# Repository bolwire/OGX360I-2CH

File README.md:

This project builds on the original OGX360 by Ryzee119: https://github.com/Ryzee119/ogx360/

The information provided in this repo is for informational purposes only at this time.

*****IMPORTANT******
The most recent prototype USB PCB required changes to be made, I have updated the schematic and PCB layout, and tested by modifying
the PCB I have on hand, however caution should be used until the new prototype is verified. Once I have verified the changes I will remove this
notice.

The ATMEGA32U4 chips will need to be programmed with the arduino bootloader before they are put on the PCB. One option may be to remove the chips
from an arduino and transplant them. I accomplish this currently by using a jig that I will release the files for at a later time.

More will be added to this repo as I find time over the next week.

Please respect the license files found within this project. What we do, and the joy we gain from that would not be possible without those who shared the
information with us to start with. Please respect and honor that by doing the same with any works derived from this or other projects linked to in this repo.

Also my spelling sucks, so I apologize for any type-ohs that exist.

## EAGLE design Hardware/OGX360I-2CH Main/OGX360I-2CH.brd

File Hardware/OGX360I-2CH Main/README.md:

# OGX360I-2CH Main PCB.
This board was designed using [Autodesk Eagle](https://www.autodesk.com/products/eagle/overview). You can edit the `.brd` and `.sch` with this program.

## Printed Circuit Board
When fabricating your own, you can download the premade gerbers or generate your own. Suggested PCB properties are:  <br>
*2 layers, 35x71mm, 1.6mm thick, HASL, 1oz copper, no castellated holes, any colour you want!*<br>

## Bill of Materials
All the passive components listed (Resistors, capacitors etc) are listed for reference only. Any equivalents you find would be suitable. Use your best judgement. 
You should check this list against the schematic to ensure nothing is missed.  
**Digikey Quick Cart: http://www.digikey.com/short/zwrw47**  

| Qty | Value/Model | Description | Marking | URL (Passive components provided as sample only) |
| --- | --- | --- | --- | --- |
| 2 | B12B-PHDSS(LF)(SN) | CONN HEADER VERT 12POS 2MM | J4,J5 | https://www.digikey.com/product-detail/en/jst-sales-america-inc/B12B-PHDSS-LF-SN/455-1763-ND/926669 |
| 1 | ‎B6B-PH-K-S(LF)(SN) | CONN HEADER VERT 6POS 2MM | J6 | https://www.digikey.com/product-detail/en/jst-sales-america-inc/B6B-PH-K-S-LF-SN/455-1708-ND/926615 |
| 1 | MIC5219-3.3YM5-TR | IC REG LINEAR 3.3V 500MA SOT23-5‎ | U3 | https://www.digikey.com/product-detail/en/microchip-technology/MIC5219-3.3YM5-TR/576-1281-1-ND/771902 |
| 9 | 08056D104KAT2A | CAP CER 0.1UF 6.3V X5R 0805 | C1,4-5,7-8,10-11,15-16 | https://www.digikey.com/product-detail/en/avx-corporation/08056D104KAT2A/478-08056D104KAT2ACT-ND/11569296 |
| 2 | CC0805JRNPO9BN180 | CAP CER 18PF 50V C0G/NPO 0805 | C2-3 | https://www.digikey.com/product-detail/en/yageo/CC0805JRNPO9BN180/311-1102-1-ND/303012 |
| 1 | EDK106M035A9BAA | CAP ALUM 10UF 20% 35V SMD | C6 | https://www.digikey.com/product-detail/en/kemet/EDK106M035A9BAA/399-14794-1-ND/7319832 |
| 2 | C0805C105Z4VACTU | CAP CER 1UF 16V Y5V 0805 | C9, C14 | https://www.digikey.com/product-detail/en/kemet/C0805C105Z4VACTU/399-8011-1-ND/3471734 |
| 4 | C0805C220J5GACTU | CAP CER 22PF 50V C0G/NP0 0805 | C12-13,17-18 | https://www.digikey.com/product-detail/en/kemet/C0805C220J5GACTU/399-1113-1-ND/411388 |
| 2 | 10118192-0001LF | CONN RCPT USB2.0 MICRO B SMD R/A | J2-3 | https://www.digikey.com/product-detail/en/amphenol-icc-fci/10118192-0001LF/609-4613-1-ND/2785378 |
| 2 | RC0805FR-0733RL | RES SMD 33 OHM 1% 1/8W 0805 | R1-2 | https://www.digikey.com/product-detail/en/yageo/RC0805FR-0733RL/311-33.0CRCT-ND/730809 |
| 2 | RC0805FR-072KL | RES SMD 2K OHM 1% 1/8W 0805 | R3-4 | https://www.digikey.com/product-detail/en/yageo/RC0805FR-072KL/311-2.00KCRCT-ND/730611 |
| 1 | RC0805JR-071KL | RES SMD 1K OHM 5% 1/8W 0805 | R5 | https://www.digikey.com/product-detail/en/yageo/RC0805JR-071KL/311-1.0KARCT-ND/731165 |
| 4 | RC0805JR-0722RL | RES SMD 22 OHM 5% 1/8W 0805 | R6-7,9-10 | https://www.digikey.com/product-detail/en/yageo/RC0805JR-0722RL/311-22ARCT-ND/731232 |
| 2 | RC0805FR-0710KL | RES SMD 10K OHM 1% 1/8W 0805 | R8,R11 | https://www.digikey.com/product-detail/en/yageo/RC0805FR-0710KL/311-10.0KCRCT-ND/730482 |
| 1 | TL3305AF160QG | SWITCH TACTILE SPST-NO 50MA 12V | RESET | https://www.digikey.com/product-detail/en/e-switch/TL3305AF160QG/EG5350CT-ND/5816195 |
| 1 | MAX3421EEHJ+T | IC USB PERIPH/HOST CNTRL 32TQFP | U1 | https://www.digikey.com/product-detail/en/maxim-integrated/MAX3421EEHJ-T/MAX3421EEHJ-TCT-ND/4895460 |
| 1 | CD74HC4050M96 | IC BUFFER NON-INVERT 6V 16SOIC | U2 | https://www.digikey.com/product-detail/en/texas-instruments/CD74HC4050M96/296-14529-1-ND/555596 |
| 2 | ATMEGA32U4-AUR | IC MCU 8BIT 32KB FLASH 44TQFP | U4-5 | https://www.digikey.com/product-detail/en/microchip-technology/ATMEGA32U4-AUR/ATMEGA32U4-AURCT-ND/3440960 |
| 2 | TSX-3225 16.0000MF09Z-AC0 | CRYSTAL 16.0000MHZ 9PF SMD | X2-3 | https://www.digikey.com/product-detail/en/epson/TSX-3225-16.0000MF09Z-AC0/SER4069CT-ND/5413938 |
| 1 | FA-238V 12.0000MB-W3 | CRYSTAL 12.0000MHZ 12PF SMD | X1 | https://www.digikey.com/product-detail/en/epson/FA-238V-12.0000MB-W3/SER3683CT-ND/2403456 |
| 2 | PHDR-12VS | CONN HOUSING PHD 12POS 2MM DUAL | --- | https://www.digikey.com/product-detail/en/jst-sales-america-inc/PHDR-12VS/455-1204-ND/608645 |
| 10 | APAPA22K152 | JUMPER SPHD-001T-P0.5 X2 6" | --- | https://www.digikey.com/product-detail/en/jst-sales-america-inc/APAPA22K152/455-3085-ND/6009461 |
| 1 | 0ZCJ0050FF2G | PTC RESET FUSE 8V 500MA 1206 | F1 | https://www.digikey.com/product-detail/en/bel-fuse-inc/0ZCJ0050FF2G/507-1802-1-ND/4156236 |
| 2 | TMUX1237DCKR | PRECISION ANALOG MULTIPLEXER | U6-7 | https://www.digikey.com/product-detail/en/texas-instruments/TMUX1237DCKR/296-TMUX1237DCKRCT-ND/12165699 |
| 1 | SM06B-SRSS-TB(LF)(SN) | CONN HEADER SMD R/A 6POS 1MM | J7 | https://www.digikey.com/product-detail/en/jst-sales-america-inc/SM06B-SRSS-TB-LF-SN/455-1806-1-ND/926877 |

## Assembled Photo

By KingLuxor

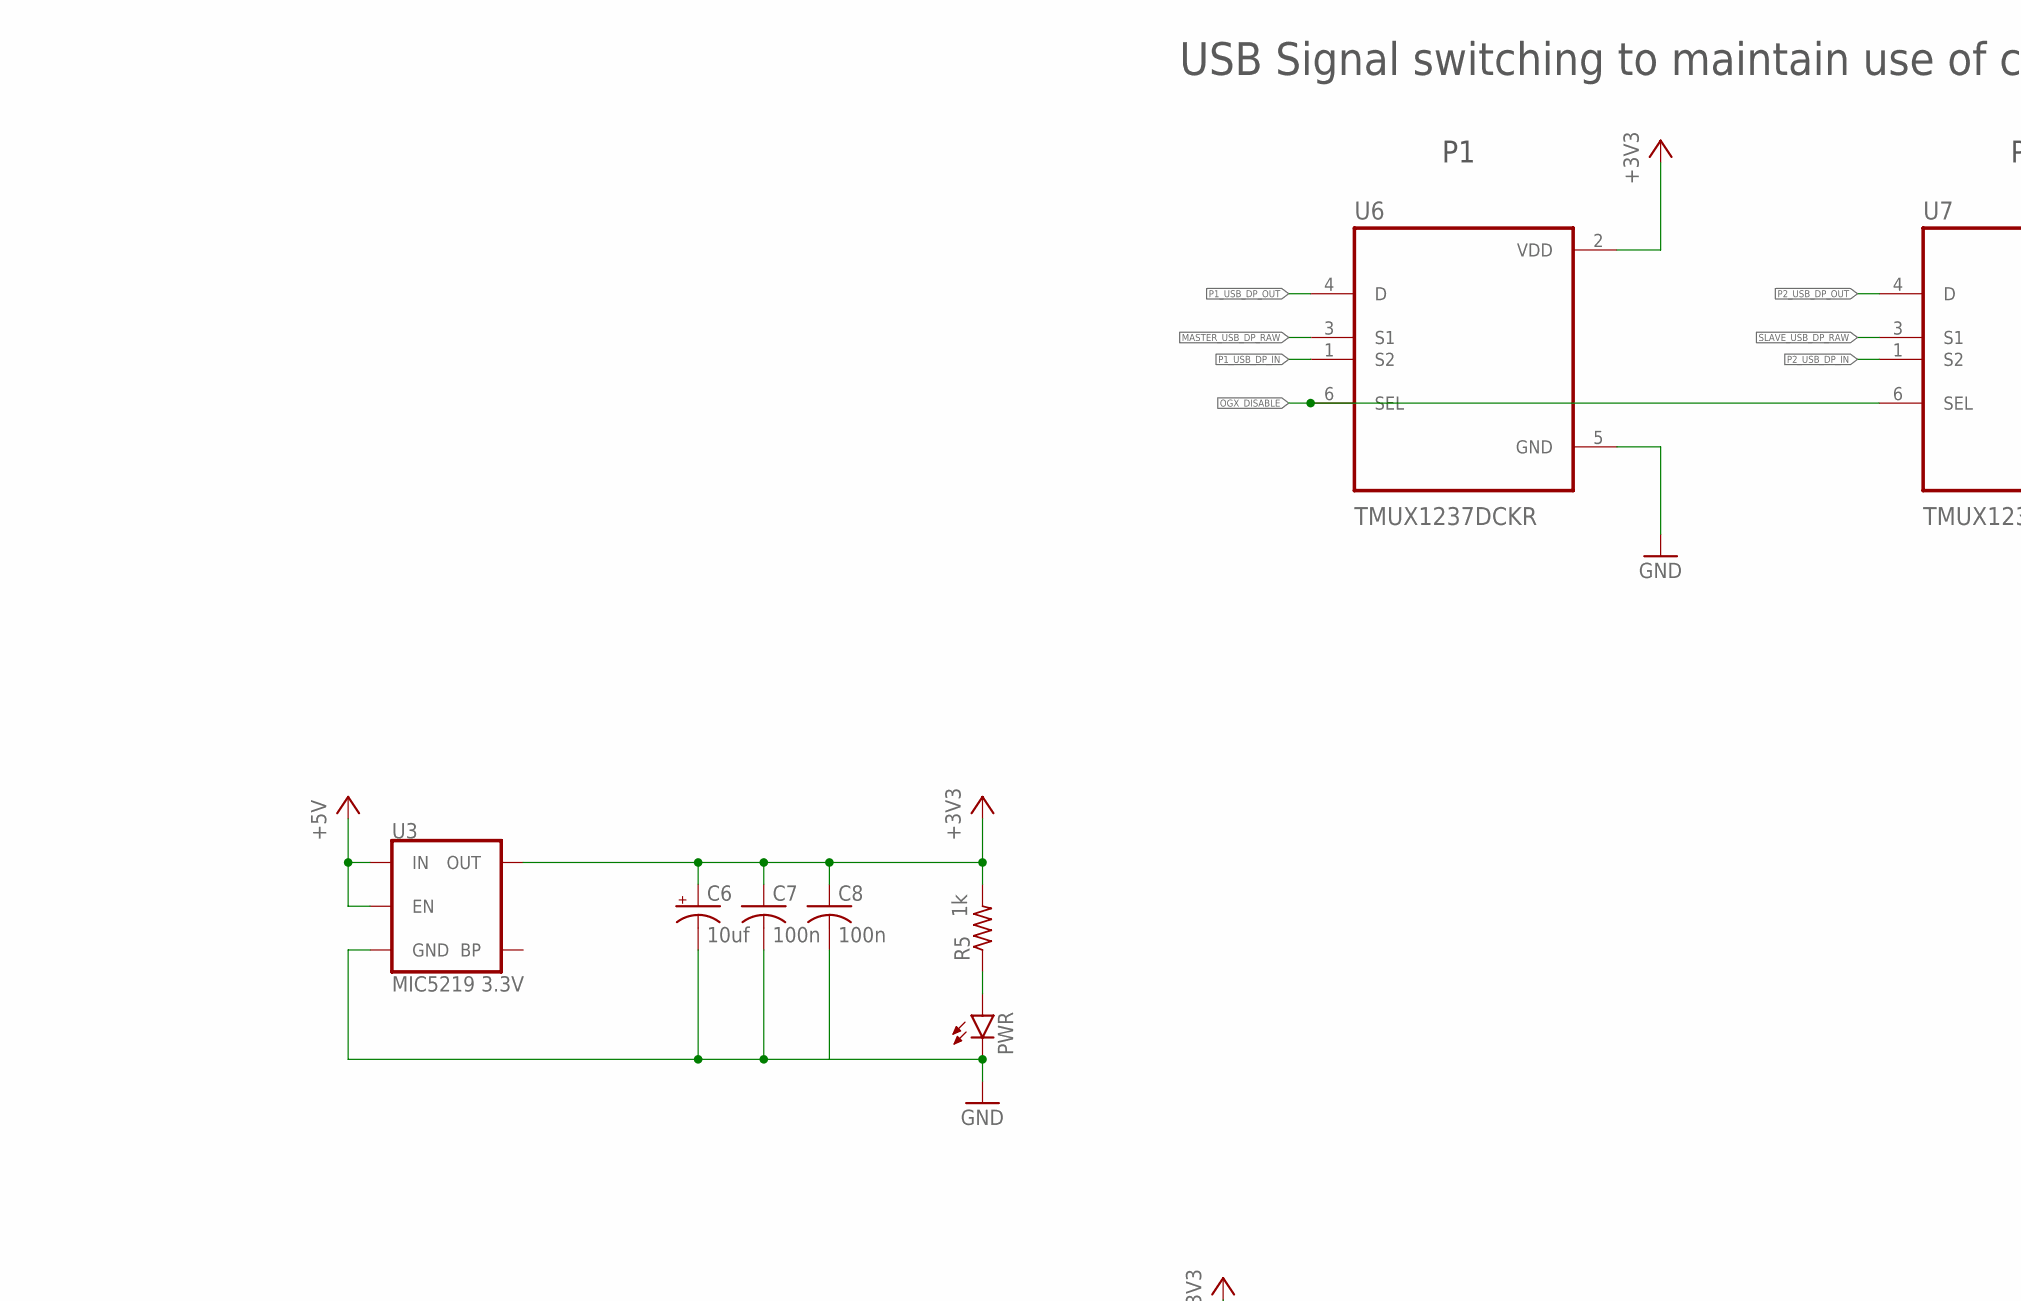
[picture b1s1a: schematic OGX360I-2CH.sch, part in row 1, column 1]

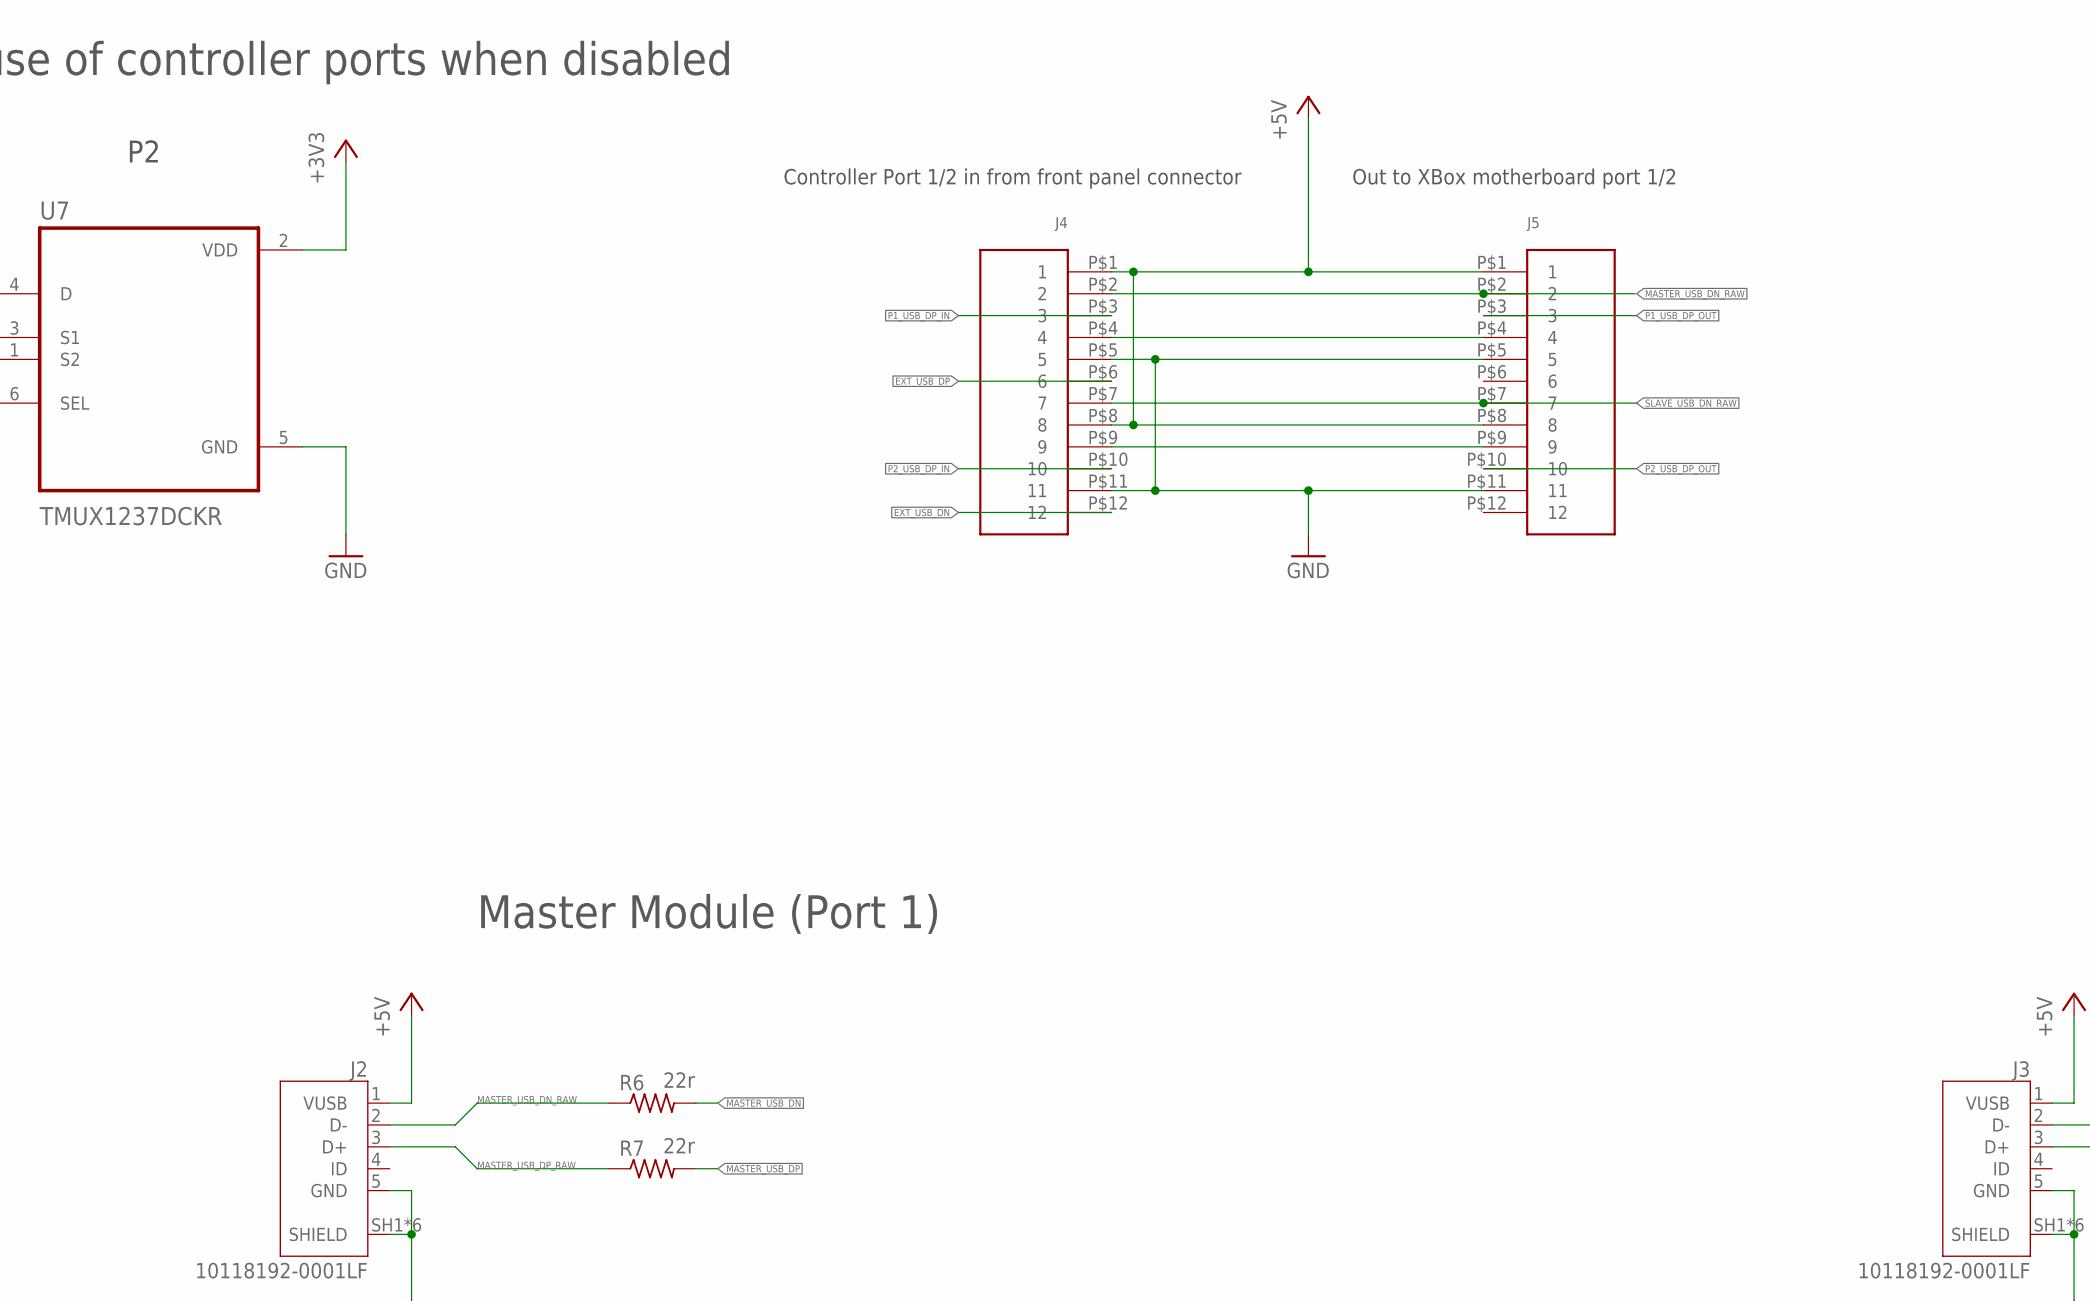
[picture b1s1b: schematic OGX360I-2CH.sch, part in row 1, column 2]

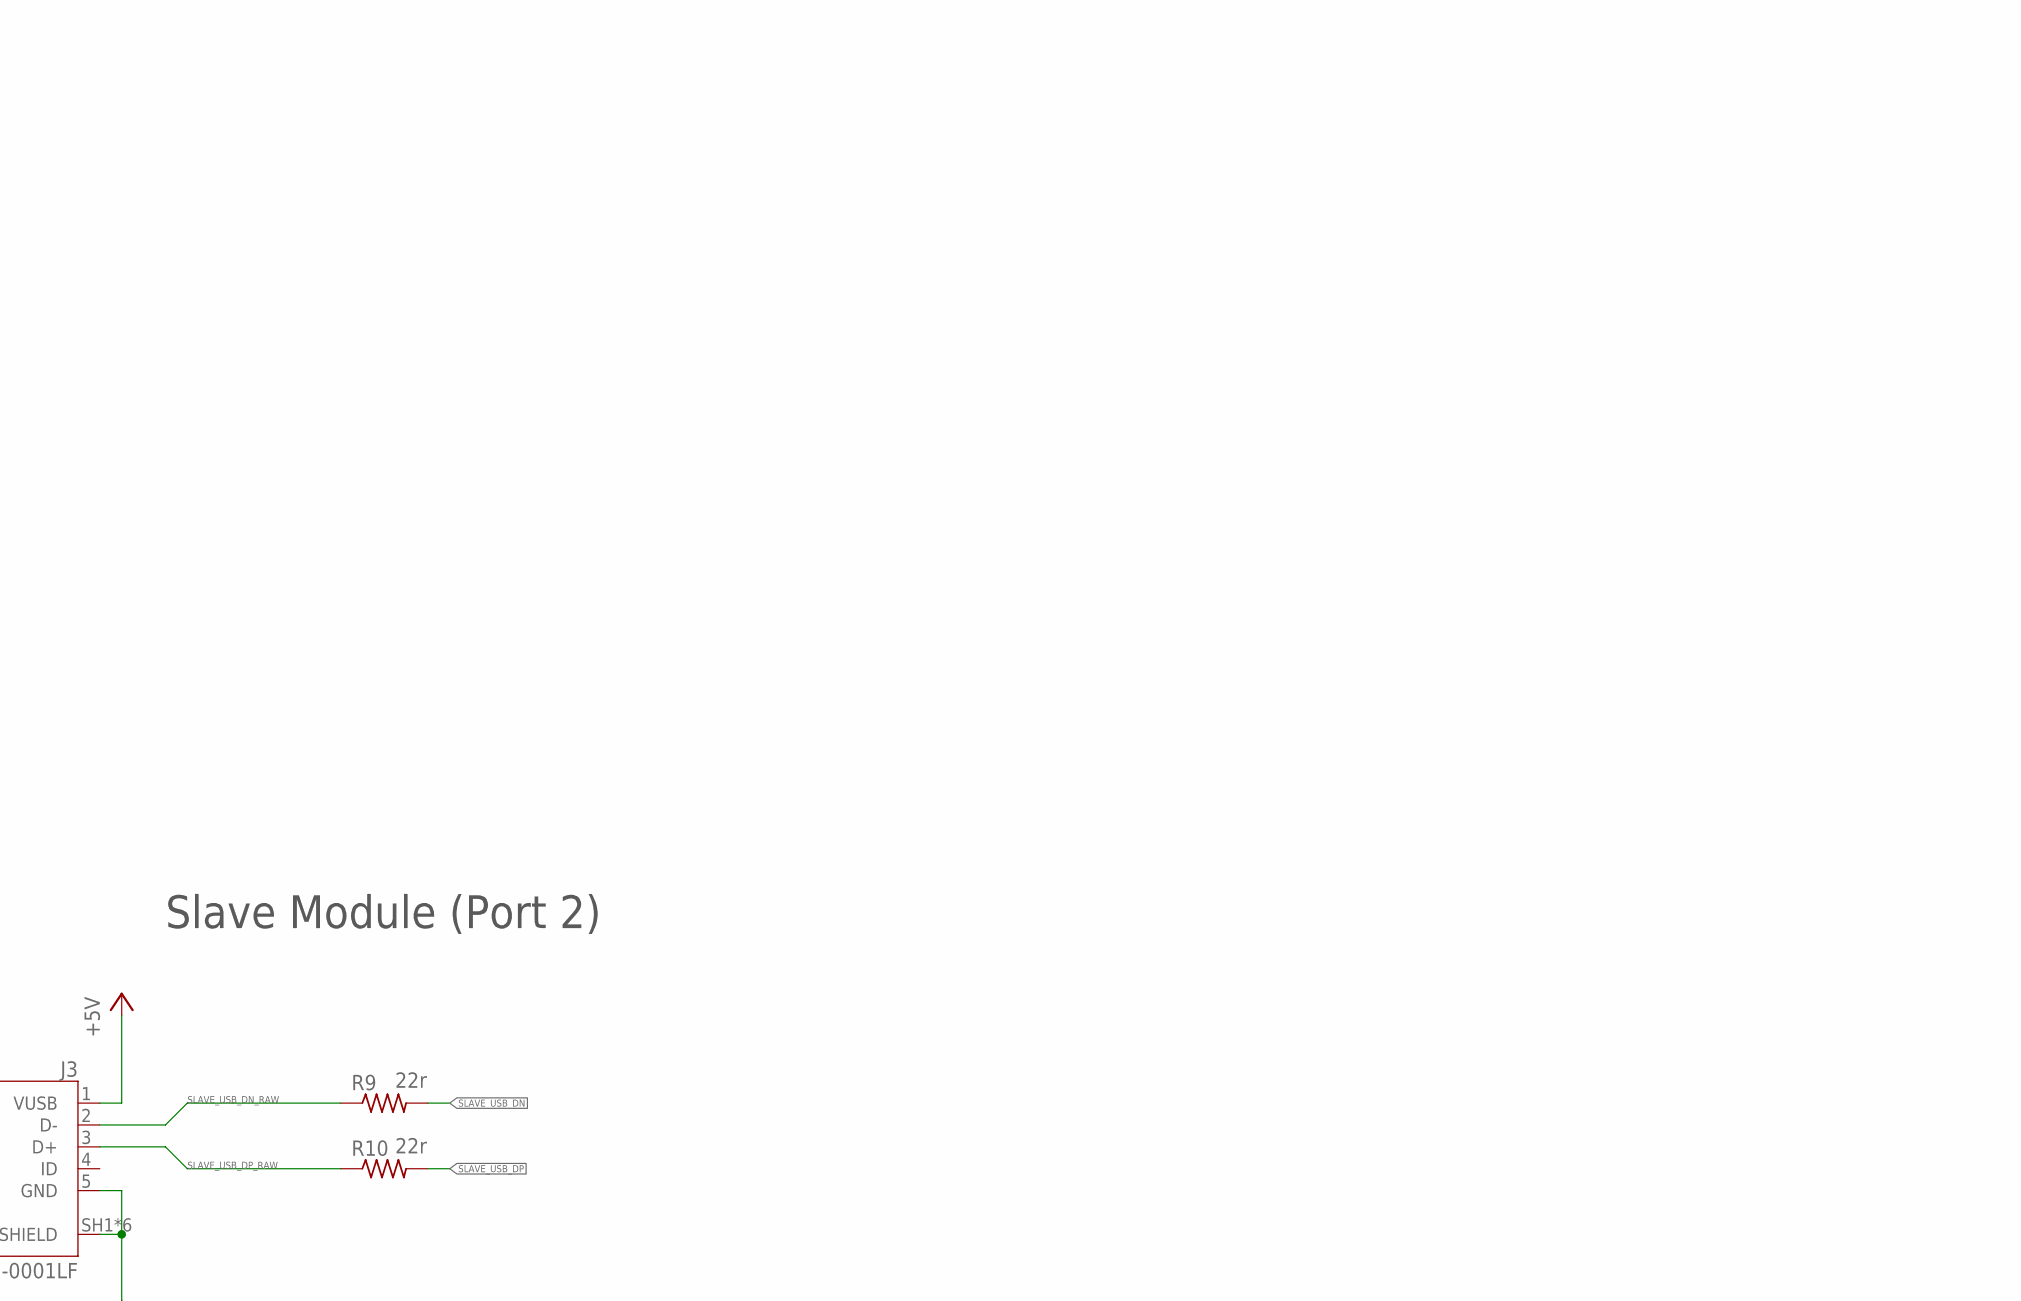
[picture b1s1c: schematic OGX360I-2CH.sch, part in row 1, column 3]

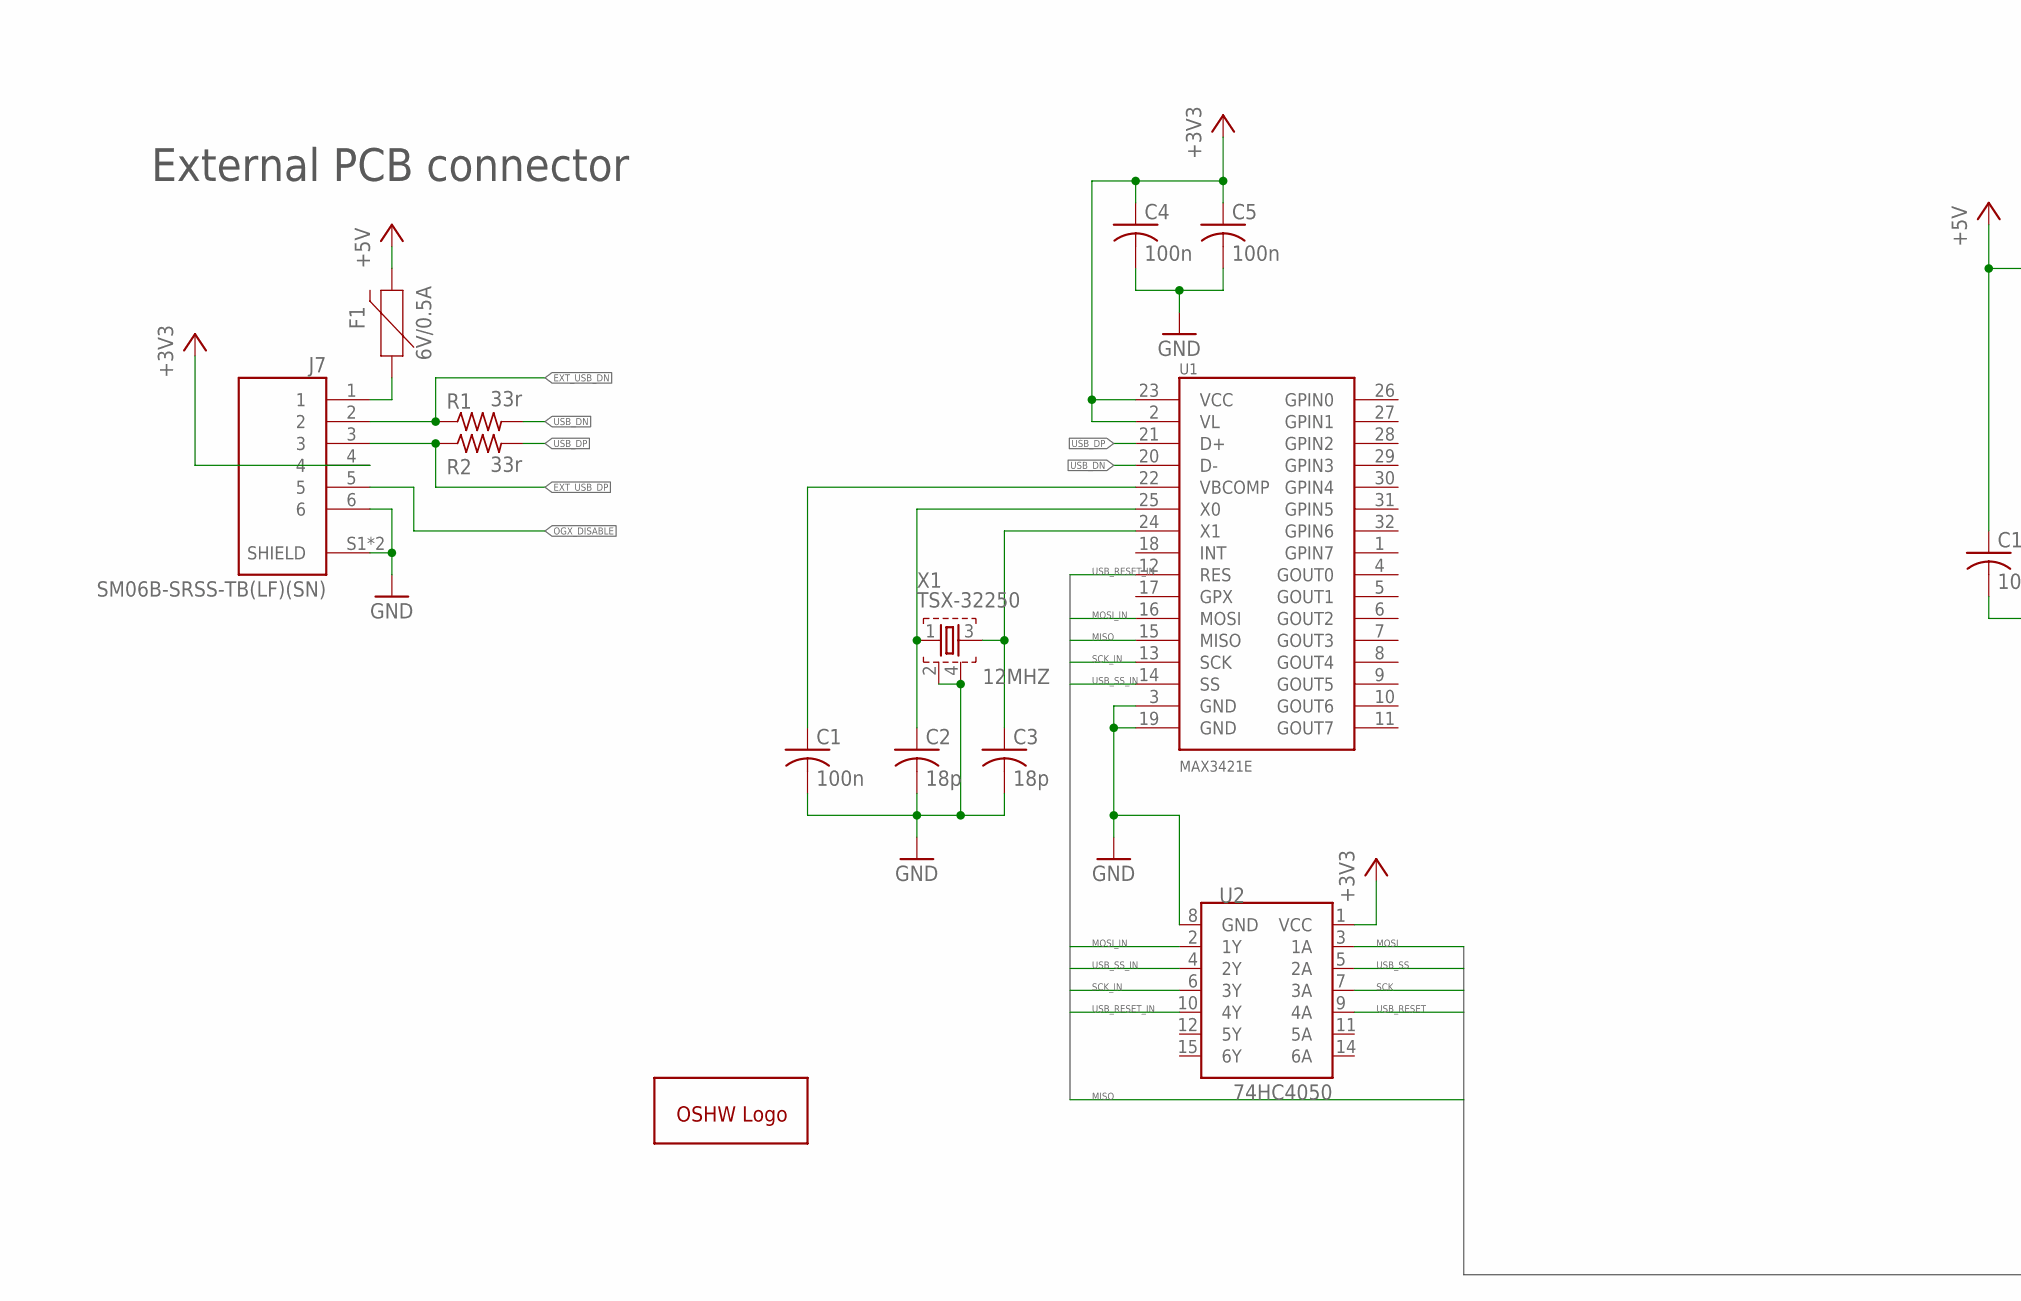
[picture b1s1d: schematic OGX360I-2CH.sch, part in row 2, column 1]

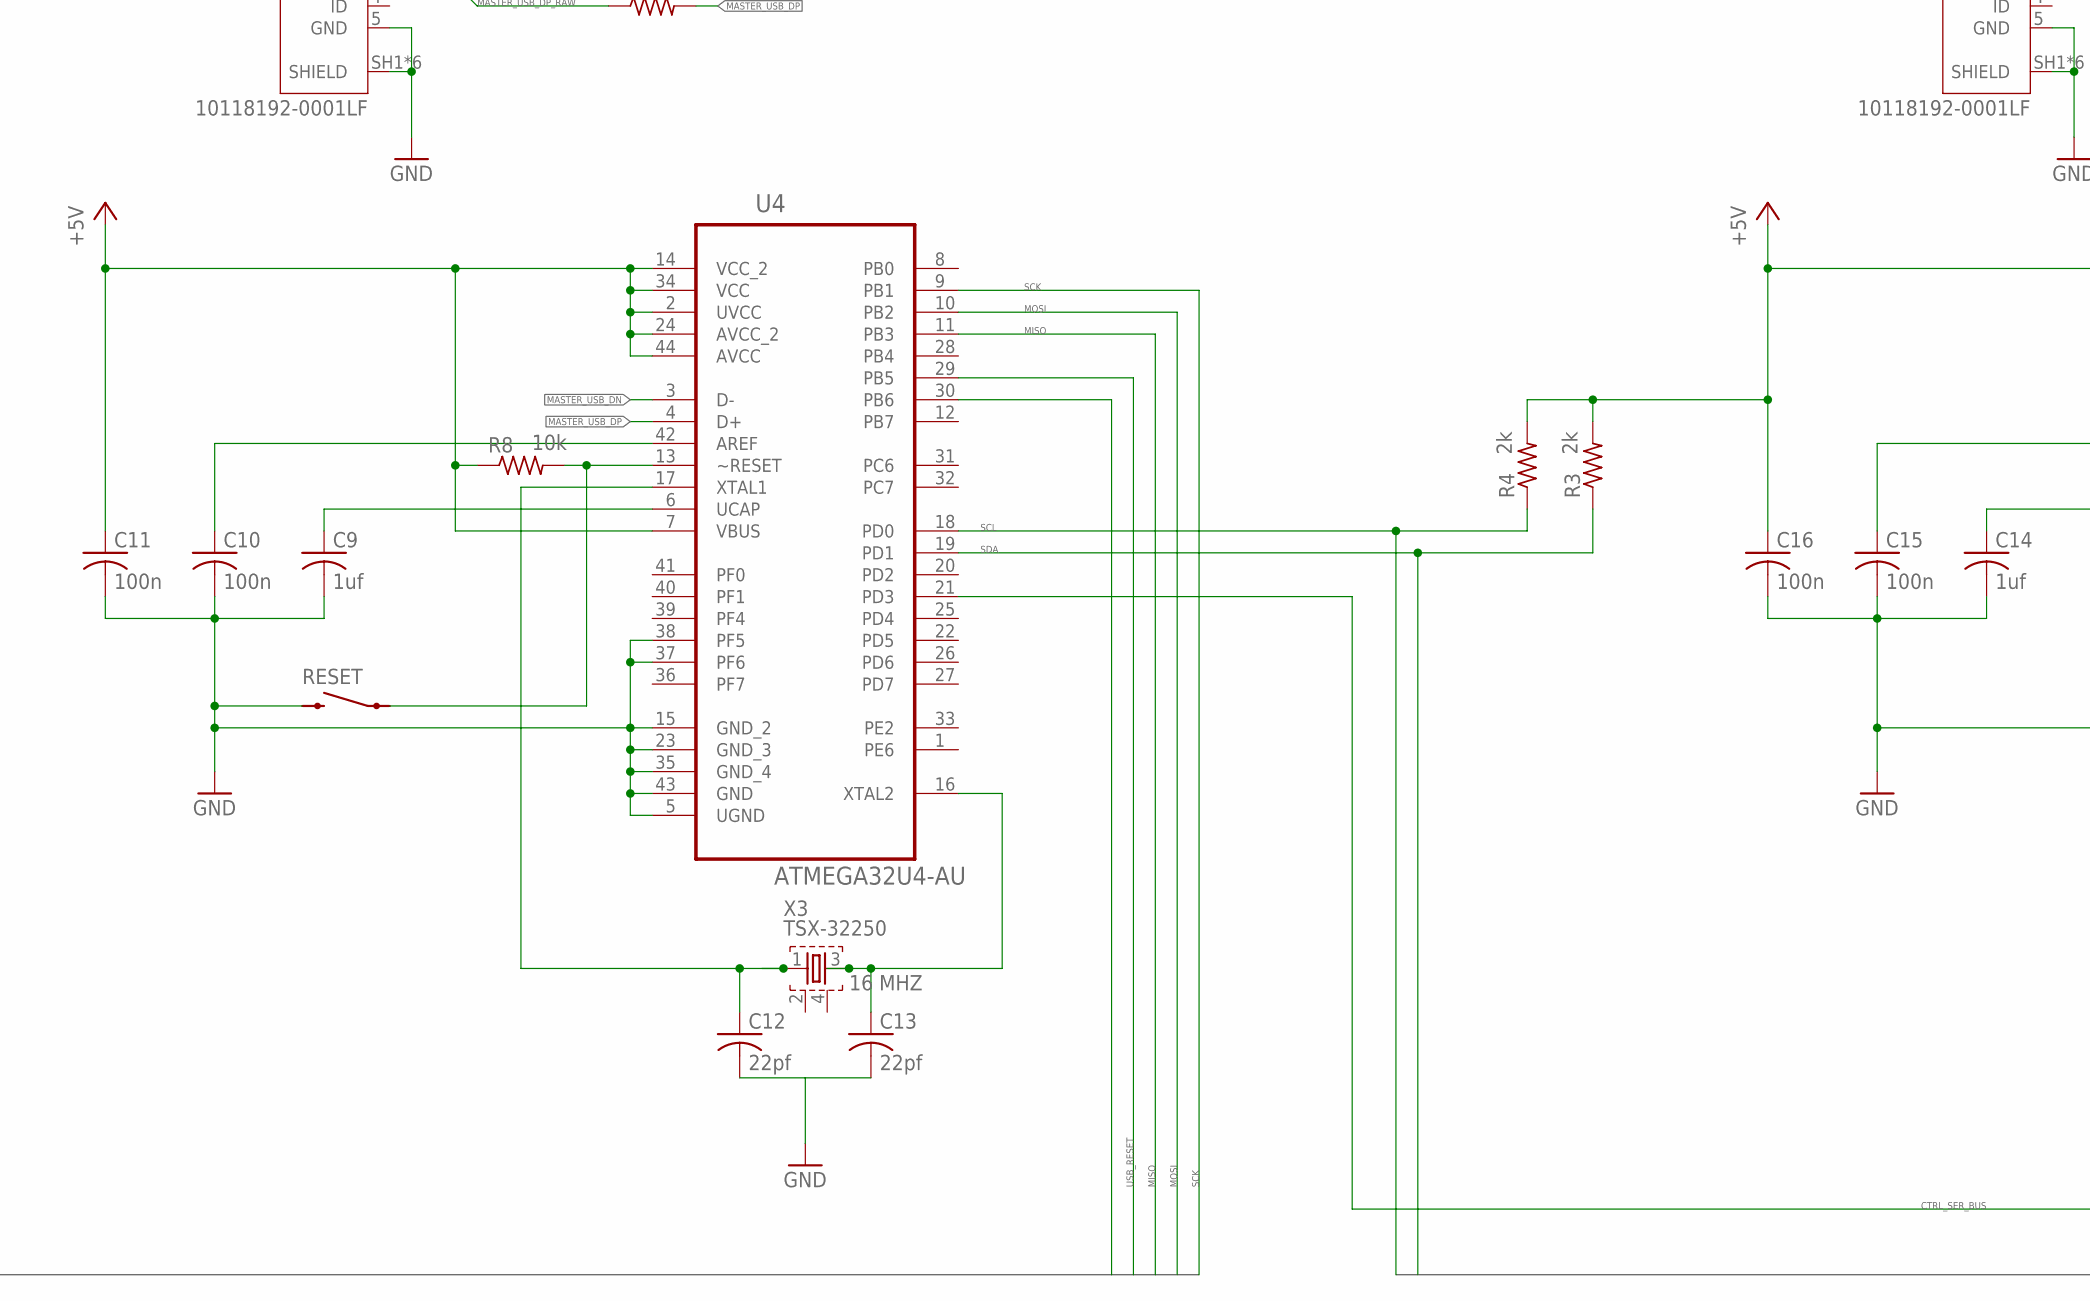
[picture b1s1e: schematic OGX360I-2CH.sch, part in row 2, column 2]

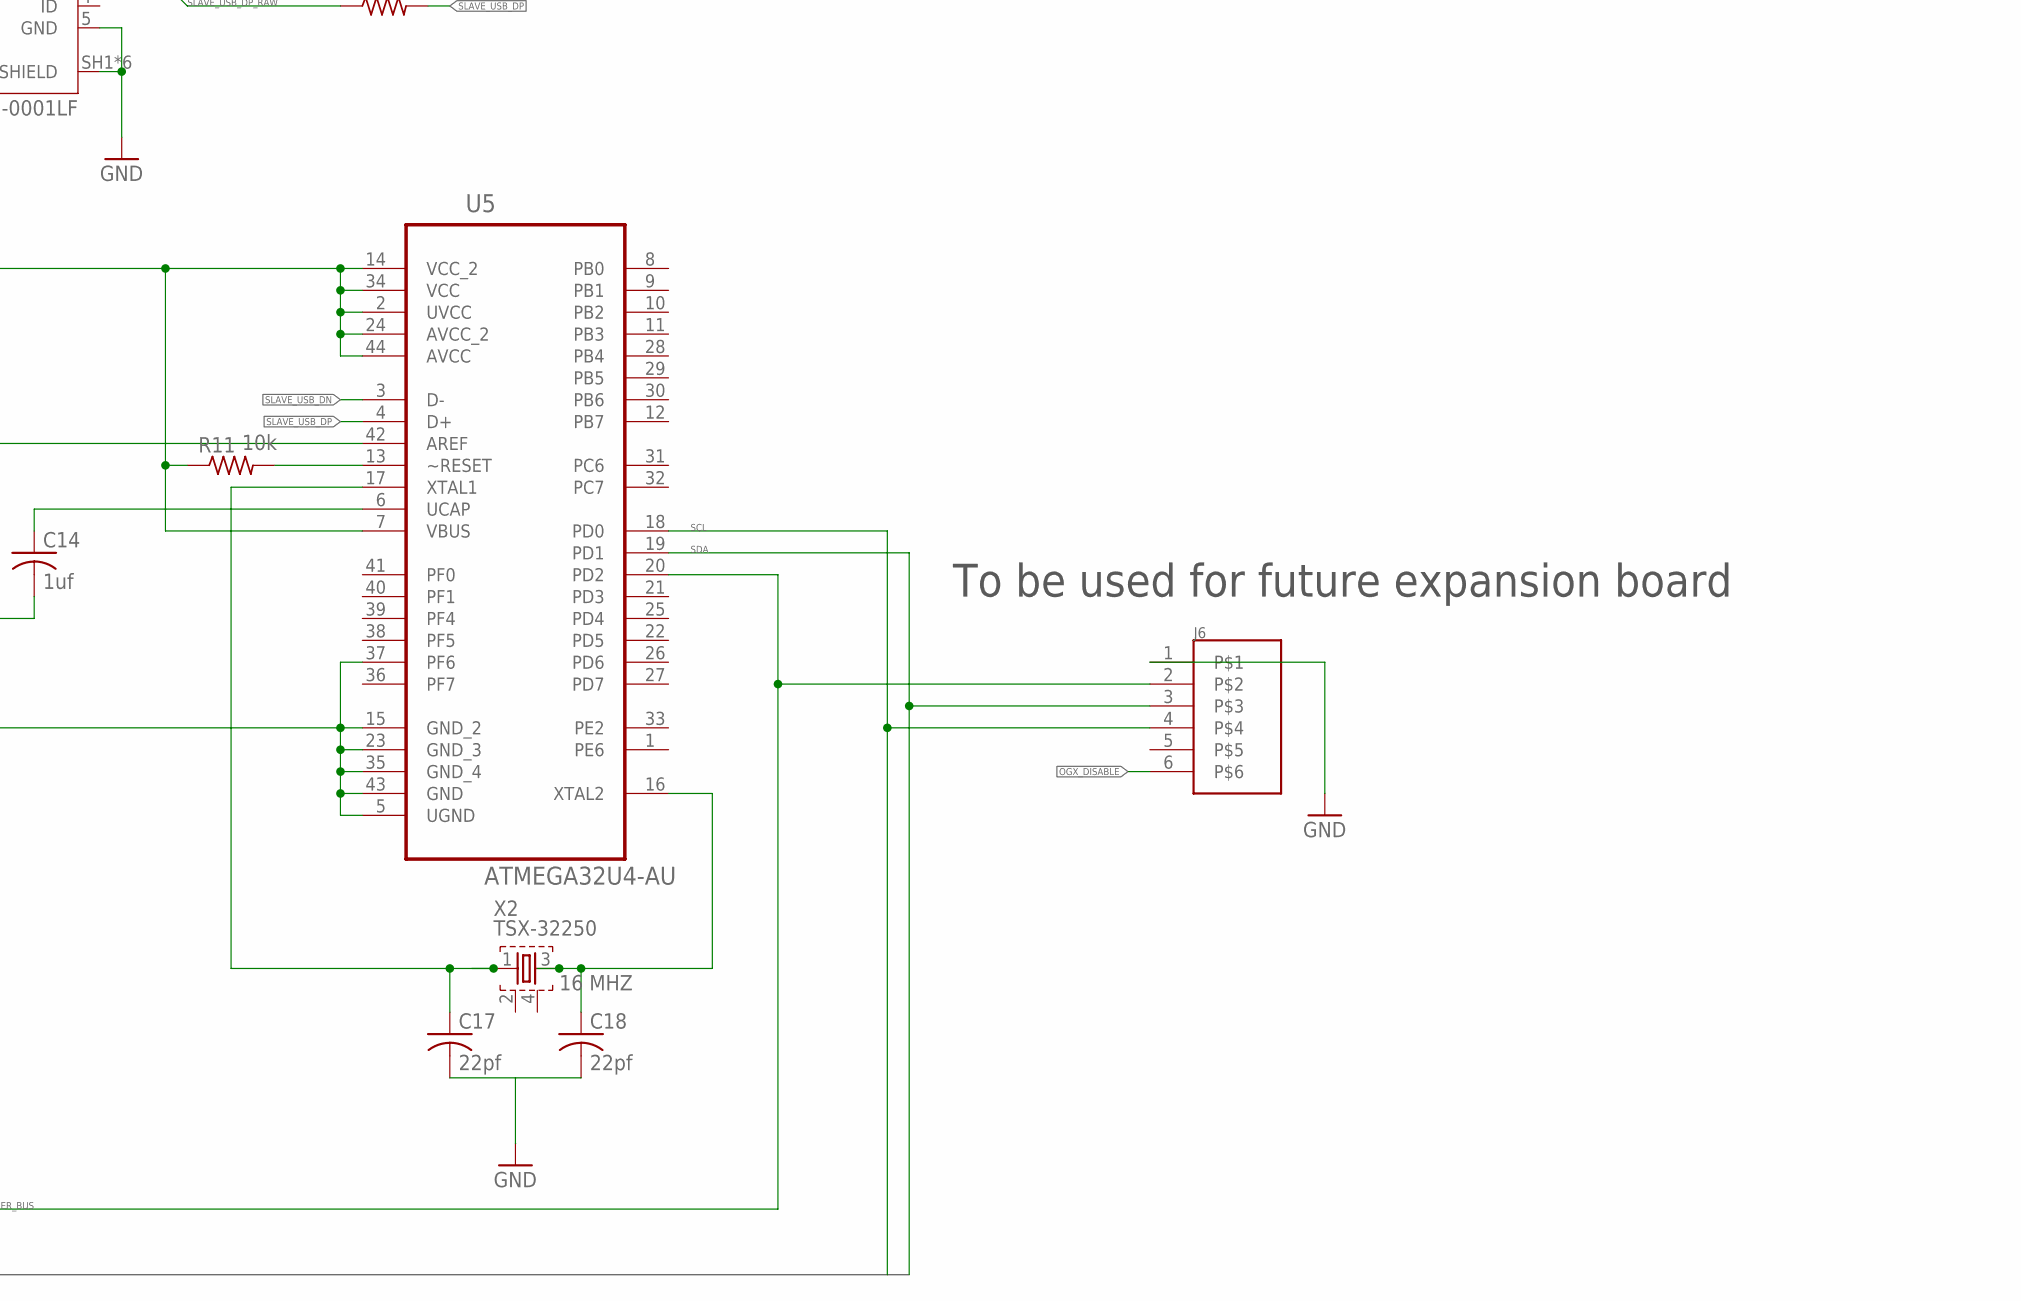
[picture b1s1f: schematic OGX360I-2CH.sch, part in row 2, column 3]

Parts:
C1, C4, C5, C7, C8, C10, C11, C15, C16: 100n; C0805
C2, C3: 18p; C0805
C6: 10uf; 153CLV-0405
C9, C14: 1uf; C0805
C12, C13, C17, C18: 22pf; C0805
F1: 6V/0.5A; 1206
GOLD_ORB_SM1: OSHWLOGOLOGO8MM; OSHW_8MM
J2, J3: 10118192-0001LF; AMPHENOL_10118192-0001LF
J4, J5: B12B-PHDSS
J6: B6B-PH-K-S; B6B-PH-K
J7: SM06B-SRSS-TB(LF)(SN); JST_SM06B-SRSS-TB(LF)(SN)
PWR: LEDCHIP-LED0805; CHIP-LED0805
R1, R2: 33r; M0805
R3, R4: 2k; M0805
R5: 1k; M0805
R6, R7, R9, R10: 22r; M0805
R8, R11: 10k; M0805
RESET: TL3305AF160QG
U1: MAX3421E; TQFP32-5MM
U2: 74HC4050; SO16
U3: MIC5219 3.3V; SOT23-5
U4, U5: ATMEGA32U4-AU; QFP80P1200X1200X120-44N
U6, U7: TMUX1237DCKR; SOT65P210X110-6N
X1, X2, X3: TSX-32250; TSX-3225

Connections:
+3V3: C4.1, C5.1, C6.+, C7.1, C8.1, J7.4, R5.2, U1.2 (VL), U1.23 (VCC), U2.1 (VCC), U3.5 (OUT), U6.2 (VDD), U7.2 (VDD)
+5V: C11.1, C16.1, F1.2, J2.1 (VUSB), J3.1 (VUSB), J4.P$1 (1), J4.P$8 (8), J5.P$1 (1), J5.P$8 (8), R3.2, R4.2, R8.1, R11.1, U3.1 (IN), U3.3 (EN), U4.2 (UVCC), U4.7 (VBUS), U4.14 (VCC_2), U4.24 (AVCC_2), U4.34 (VCC), U4.44 (AVCC), U5.2 (UVCC), U5.7 (VBUS), U5.14 (VCC_2), U5.24 (AVCC_2), U5.34 (VCC), U5.44 (AVCC)
CTRL_SER_BUS: J6.2, U4.21 (PD3), U5.20 (PD2)
EXT_USB_DN: J4.P$12 (12), J7.2, R1.1
EXT_USB_DP: J4.P$6 (6), J7.3, R2.1
GND: C1.2, C2.2, C3.2, C4.2, C5.2, C6.-, C7.2, C8.2, C9.2, C10.2, C11.2, C12.2, C13.2, C14.2, C15.2, C16.2, C17.2, C18.2, J2.5 (GND), J2.SH1 (SHIELD), J2.SH2 (SHIELD), J2.SH3 (SHIELD), J2.SH4 (SHIELD), J2.SH5 (SHIELD), J2.SH6 (SHIELD), J3.5 (GND), J3.SH1 (SHIELD), J3.SH2 (SHIELD), J3.SH3 (SHIELD), J3.SH4 (SHIELD), J3.SH5 (SHIELD), J3.SH6 (SHIELD), J4.P$5 (5), J4.P$11 (11), J5.P$5 (5), J5.P$11 (11), J6.1, J7.6, J7.S1 (SHIELD), J7.S2 (SHIELD), PWR.C, RESET.P$1, RESET.P$2, U1.3 (GND), U1.19 (GND), U2.8 (GND), U3.2 (GND), U4.5 (UGND), U4.15 (GND_2), U4.23 (GND_3), U4.35 (GND_4), U4.37 (PF6), U4.38 (PF5), U4.43 (GND), U5.5 (UGND), U5.15 (GND_2), U5.23 (GND_3), U5.35 (GND_4), U5.37 (PF6), U5.43 (GND), U6.5 (GND), U7.5 (GND), X1.2, X1.4
MASTER_USB_DN: R6.2, U4.3 (D-)
MASTER_USB_DN_RAW: J2.2 (D-), J4.P$2 (2), J5.P$2 (2), R6.1
MASTER_USB_DP: R7.2, U4.4 (D+)
MASTER_USB_DP_RAW: J2.3 (D+), R7.1, U6.3 (S1)
MISO: U1.15 (MISO), U4.11 (PB3)
MOSI: U2.3 (1A), U4.10 (PB2)
MOSI_IN: U1.16 (MOSI), U2.2 (1Y)
unnamed: C13.1, U4.16 (XTAL2), X3.3
unnamed: C3.1, U1.24 (X1), X1.3
unnamed: F1.1, J7.1
unnamed: PWR.A, R5.1
unnamed: C2.1, U1.25 (X0), X1.1
unnamed: C1.1, U1.22 (VBCOMP)
unnamed: C9.1, U4.6 (UCAP)
unnamed: C10.1, U4.42 (AREF)
unnamed: C12.1, U4.17 (XTAL1), X3.1
unnamed: C14.1, U5.6 (UCAP)
unnamed: C15.1, U5.42 (AREF)
unnamed: C18.1, U5.16 (XTAL2), X2.3
unnamed: C17.1, U5.17 (XTAL1), X2.1
unnamed: J4.P$4 (4), J5.P$4 (4)
unnamed: J4.P$9 (9), J5.P$9 (9)
OGX_DISABLE: J6.6, J7.5, U6.6 (SEL), U7.6 (SEL)
P1_USB_DP_IN: J4.P$3 (3), U6.1 (S2)
P1_USB_DP_OUT: J5.P$3 (3), U6.4 (D)
P2_USB_DP_IN: J4.P$10 (10), U7.1 (S2)
P2_USB_DP_OUT: J5.P$10 (10), U7.4 (D)
RESET: R8.2, R11.2, RESET.P$3 (2), RESET.P$4 (2), U4.13 (~RESET), U5.13 (~RESET)
SCK: U2.7 (3A), U4.9 (PB1)
SCK_IN: U1.13 (SCK), U2.6 (3Y)
SCL: J6.4, R4.1, U4.18 (PD0), U5.18 (PD0)
SDA: J6.3, R3.1, U4.19 (PD1), U5.19 (PD1)
SLAVE_USB_DN: R9.2, U5.3 (D-)
SLAVE_USB_DN_RAW: J3.2 (D-), J4.P$7 (7), J5.P$7 (7), R9.1
SLAVE_USB_DP: R10.2, U5.4 (D+)
SLAVE_USB_DP_RAW: J3.3 (D+), R10.1, U7.3 (S1)
USB_DN: R1.2, U1.20 (D-)
USB_DP: R2.2, U1.21 (D+)
USB_RESET: U2.9 (4A), U4.29 (PB5)
USB_RESET_IN: U1.12 (RES), U2.10 (4Y)
USB_SS: U2.5 (2A), U4.30 (PB6)
USB_SS_IN: U1.14 (SS), U2.4 (2Y)

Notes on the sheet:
Controller Port 1/2 in from front panel connector
Out to XBox motherboard port 1/2
12MHZ
16 MHZ
USB Signal switching to maintain use of controller ports when disabled
External PCB connector
Master Module (Port 1)
Slave Module (Port 2)
To be used for future expansion board

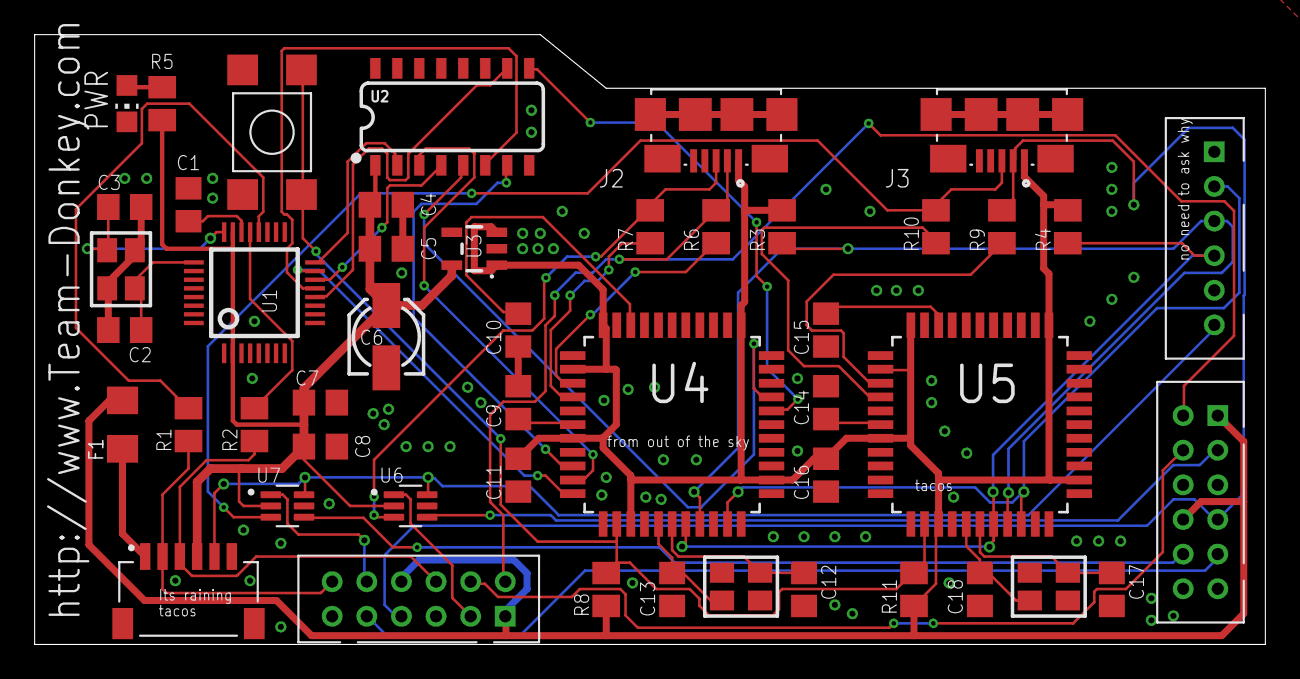
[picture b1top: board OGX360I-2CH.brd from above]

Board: 2 copper layers, 71.1 x 35.2 mm, 49 parts (1 on the bottom side), 48 nets.

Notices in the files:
parts and their libraries:
SparkFun-Fuses: Licensing: Creative Commons ShareAlike 4.0 International - https://creativecommons.org/licenses/by-sa/4.0
